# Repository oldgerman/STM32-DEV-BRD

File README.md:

# STM32-DEV-BRD

（白嫖失败血压升高后）整的几片考究的STM32最小系统板，~~清一色0603~~，确保食用舒适

PCB工程完全开源，提供测试程序，焊接后第一时间可刷入测试

## 型号

- 💚：完工并已验证
- :yellow_heart:：完工但未验证
- :x:：还没画板子

| 更新日期   | 状态           | 开发板型号                                                   | 支持芯片                                                 | PCB层数 |
| ---------- | -------------- | ------------------------------------------------------------ | -------------------------------------------------------- | ------- |
| 2022/04/29 | 💚              | [G031 DEV BRD](https://github.com/oldgerman/STM32-DEV-BRD/tree/master/G031_Dev) | STM32G031G8Ux                                            | 2       |
| 2022/04/29 | 💚              | [F4x1 DEV BRD](https://github.com/oldgerman/STM32-DEV-BRD/tree/master/F4x1_Dev) | STM32F401CxUx<br />STM32F411CxUx                         | 4       |
| 2022/07/31 | :yellow_heart: | [H7xxVxT6_LANG](https://github.com/oldgerman/STM32-DEV-BRD/tree/master/H7xxVxT6_LANG) | （LQFP100）<br />STM32H750<br />STM32H743<br />STM32H7B0 | 2       |
| ?          | :x:            | F07x DEV BRD                                                 | STM32F071CxUx<br />STM32F072CxUx                         | ?       |
| ?          | :x:            | F103 DEV BRD                                                 | STM32F103CxUx                                            | ?       |
| 2024/02/29 | 💚              | [G431 DEV BRD](https://github.com/oldgerman/STM32-DEV-BRD/tree/master/G431_Dev) | STM32G431GBUx                                            | 4       |
| ?          | ...            | （不定期更新）                                               |                                                          |         |

## PCB

| 开发板型号   | Top                                                          | Bottom                                                       |
| ------------ | ------------------------------------------------------------ | ------------------------------------------------------------ |
| G031 DEV BRD |  |  |
| F4x1 DEV BRD |  |  |
| G431 DEV BRD |  |  |

## 图片

.jpeg)

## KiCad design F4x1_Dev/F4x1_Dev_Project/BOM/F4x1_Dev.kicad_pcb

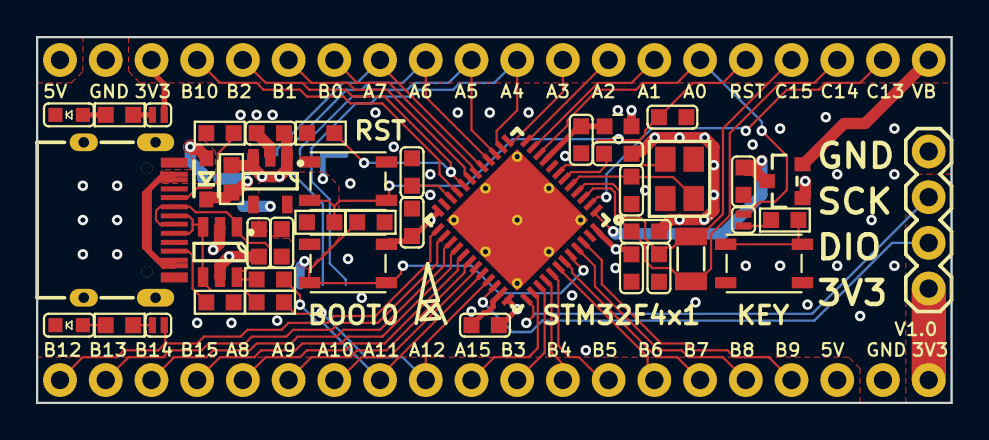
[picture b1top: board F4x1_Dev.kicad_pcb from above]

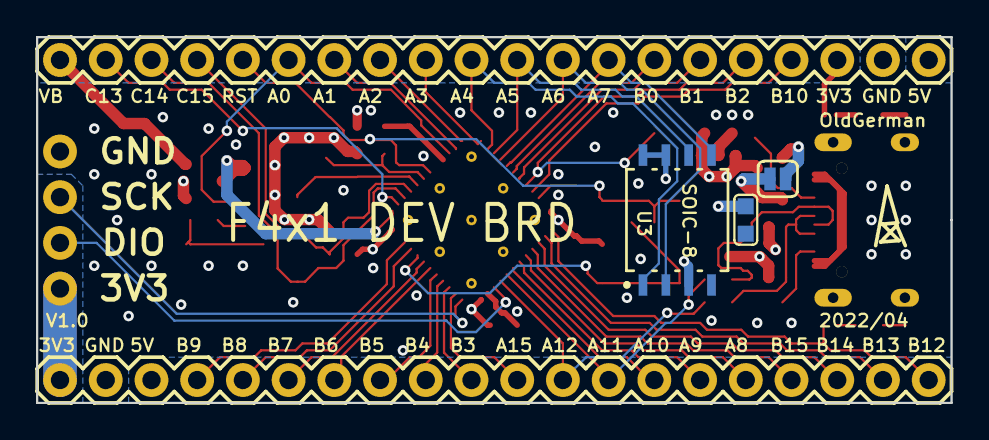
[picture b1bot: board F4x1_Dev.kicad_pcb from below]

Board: 4 copper layers, 50.8 x 20.3 mm, 50 parts (6 on the bottom side), 57 nets.

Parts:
*1, *2: ODG_LOGO; ODG_LOGO_1
C1, C4, C5, C6, C9, C14, C15: 100nF; C0603_1
C2, C3: 1uF/X7R; C0603_1
C7: 100nF; C0603_2
C8, C10: 6pF; C0603_1
C11, C13: 10pF; C0603_1
C12: 2.2uF; C0603_1
D1: B5819W; SOD-323_1
F1: 6V/0.5A; FUSE0603_0.5MM_1
L1: 10uH; FER0603_1
LED1: LED; LED0603_GREEN_1
LED2: LED; LED0603_YELLOW_1
P1, P2: CONN_X20; 2.54MM_MALE_X20_1
P3: CONN_X4; 2.54mm_Male_x4_1
R1, R2, R3, R4: 5.1K; R0603_1
R5, R6: 22R; R0603_1
R7: 330R; R0603_1
R8, R9, R10: 10K; R0603_1
SJ1: SJ_2P; SJ_2P_1
SJ2, SJ3, SJ4: SJ_2P; SJ_2P_MINI_1
SW1, SW2, SW3: Button-4P; SWITCH_3X4X2.5_4PIN_SMD_1
U1: STM32F4x1CxU6; UFQFPN-48_7X7X0P55MM_VIA_1
U2: ME6211C33M5G; ANALOG_TSOT-23-5_UJ-5_1
U3: W25Q32JVSSIQ; WIN_SS-8_WIN-L_1
USB1: Type-C; Type-C-TOP_1
VD1: BAT54C; ON_SEMI_SOT-23-3_1
VD2: USBLC6-2; MICROCHIP_SOT-23-6_M6_1
X1: 32.768KHz; XTAL_2P_3215_1
X2: 8MHz; EPSON_TSX-3225_1

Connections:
+3V3: C3.2, C4.2, C5.1, C6.1, C15.2, L1.1, P1.20, P2.3, P3.1, R9.1, SJ2.1, SW3.3, SW3.4, U1.24, U1.36, U1.48, U2.5, U3.3, U3.7, U3.8, VD1.1
+5: D1.1, SJ1.1, USB1.A4, USB1.A9, USB1.B4, USB1.B9
BOOT0: R10.1, SW3.1, SW3.2, U1.44
D+: R6.1, USB1.A6, USB1.B6, VD2.3, VD2.4
D-: R5.1, USB1.A7, USB1.B7, VD2.1, VD2.6
F_CS: P2.11, U1.14, U3.1
GND: C1.2, C2.1, C3.1, C4.1, C5.2, C6.2, C7.1, C8.2, C9.1, C10.2, C11.2, C12.1, C13.2, C14.1, C15.1, LED1.2, LED2.2, P1.19, P2.2, P3.4, R1.1, R3.2, R8.2, R10.2, SW1.3, SW1.4, SW2.1, SW2.2, U1.8, U1.23, U1.35, U1.47, U1.49, U1.49_1, U1.49_2, U1.49_3, U1.49_4, U1.49_5, U1.49_6, U1.49_7, U1.49_8, U1.49_9, U2.2, U3.4, USB1.1, USB1.2, USB1.3, USB1.4, USB1.A1, USB1.A12, USB1.B1, USB1.B12, VD2.2, X2.2, X2.4
MISO: P2.9, U1.16, U3.2
MOSI: P2.8, U1.17, U3.5
NRST: C14.2, P2.16, R9.2, SW2.3, SW2.4, U1.7
NetC12_2: C12.2, U1.22
NetD1_2: D1.2, F1.1, SJ1.2
NetLED1_1: LED1.1, R2.2
NetLED2_1: LED2.1, R4.2
NetR1_2: R1.2, USB1.A5
NetR2_1: R2.1, SJ2.2
NetR3_1: R3.1, USB1.B5
NetR4_1: R4.1, SJ3.2
NetR7_1: R7.1, SW1.1, SW1.2
NetR7_2: R7.2, SJ4.2
PA0: P2.15, SJ4.1, U1.10
PA1: P2.14, U1.11
PA2: P2.13, U1.12
PA3: P2.12, U1.13
PA5: P2.10, U1.15, U3.6
PA8: P1.5, U1.29
PA9: P1.6, U1.30
PA10: P1.7, U1.31
PA11: P1.8, R5.2, U1.32
PA12: P1.9, R6.2, U1.33
PA13: P3.2, U1.34
PA14: P3.3, U1.37
PA15: P1.10, U1.38
PB0: P2.7, U1.18
PB1: P2.6, U1.19
PB2: P2.5, R8.1, U1.20
PB3: P1.11, U1.39
PB4: P1.12, U1.40
PB5: P1.13, U1.41
PB6: P1.14, U1.42
PB7: P1.15, U1.43
PB8: P1.16, U1.45
PB9: P1.17, U1.46
PB10: P2.4, U1.21
PB12: P1.1, SJ3.1, U1.25
PB13: P1.2, U1.26
PB14: P1.3, U1.27
PB15: P1.4, U1.28
PC13: P2.19, U1.2
PC14: C8.1, P2.18, U1.3, X1.1
PC15: C10.1, P2.17, U1.4, X1.2
PH0: C11.1, U1.5, X2.1
PH1: C13.1, U1.6, X2.3
VB: P2.20, VD1.2
VBAT: C1.1, U1.1, VD1.3
VCC: C2.2, C9.2, F1.2, P1.18, P2.1, U2.1, U2.3, VD2.5
VREF+: C7.2, L1.2, U1.9

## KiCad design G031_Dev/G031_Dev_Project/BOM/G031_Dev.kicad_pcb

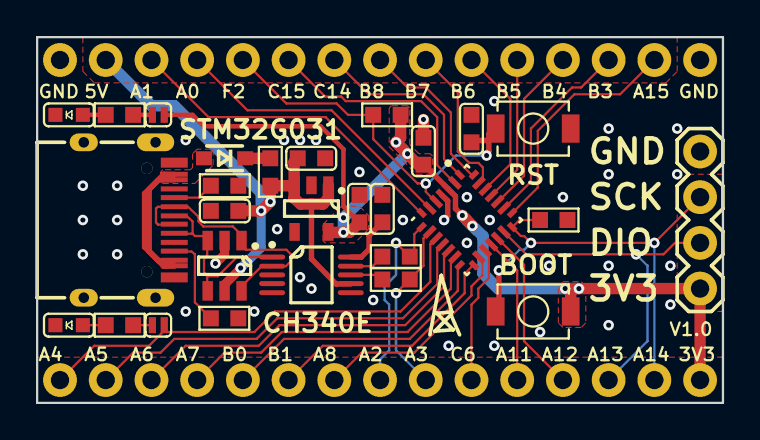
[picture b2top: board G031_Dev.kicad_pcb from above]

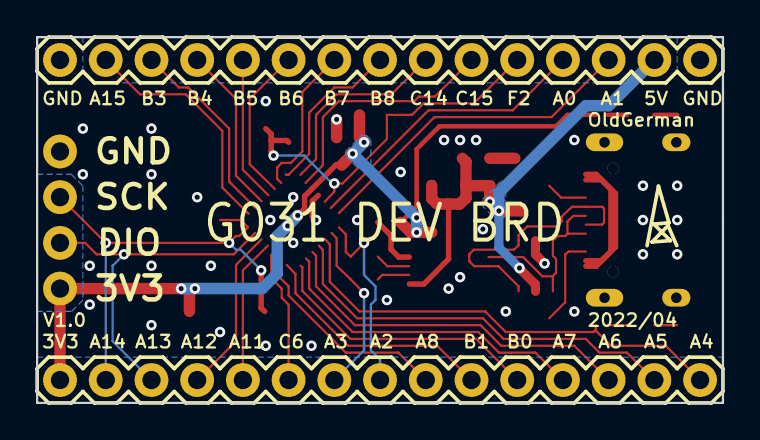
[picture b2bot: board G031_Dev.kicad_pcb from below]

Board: 2 copper layers, 38.1 x 20.3 mm, 32 parts (3 on the bottom side), 42 nets.

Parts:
*, *2: ODG_LOGO; ODG_LOGO_1
C1, C3, C4: 100nF; C0603_1
C2: 1uF/X7R; C0603_2
C5, C6: 1uF/X7R; C0603_1
D1: B5819W; SOD-323_1
F1: 6V/0.5A; FUSE0603_0.5MM_1
LED1: LED; LED0603_GREEN_1
LED2: LED; LED0603_YELLOW_1
P1: CONN_X4; 2.54mm_Male_x4_1
P2, P3: CONN_X15; 2.54MM_MALE_X15_1
R1, R2, R3, R8: 5.1K; R0603_1
R4, R5: 470R; R0603_1
R6, R7: 10K; R0603_1
SJ1, SJ2: SJ_2P; SJ_2P_MINI_1
SW1, SW2: Button-2P; SWITCH_3X4_SMD_1
U1: STM32G031G8U6; UFQFPN28-4x4mm_ODG_1
U2: CH340E; TI_MSOP-10_DGS_1
U3: ME6211C33M5G; ANALOG_TSOT-23-5_UJ-5_1
USB1: Type-C; Type-C-TOP_1
VD1: USBLC6-2; MICROCHIP_SOT-23-6_M6_1

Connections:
+3V3: C2.1, C6.2, P1.1, P2.15, R6.1, SJ1.1, SW1.2, U1.3, U3.5
+5: D1.1, USB1.A4, USB1.A9, USB1.B4, USB1.B9
CH340E_RX: R5.1, U2.9
CH340E_TX: R4.1, U2.8
D+: U2.1, USB1.A6, USB1.B6, VD1.3, VD1.4
D-: U2.2, USB1.A7, USB1.B7, VD1.1, VD1.6
GND: C1.1, C2.2, C3.1, C4.1, C5.1, C6.1, LED1.2, LED2.2, P1.4, P3.1, P3.15, R2.1, R3.2, R7.2, SW2.1, U1.4, U2.3, U3.2, USB1.1, USB1.2, USB1.3, USB1.4, USB1.A1, USB1.A12, USB1.B1, USB1.B12, VD1.2
NetC1_2: C1.2, U2.10
NetD1_2: D1.2, F1.1
NetLED1_1: LED1.1, R1.2
NetLED2_1: LED2.1, R8.2
NetR1_1: R1.1, SJ1.2
NetR2_2: R2.2, USB1.A5
NetR3_1: R3.1, USB1.B5
NetR8_1: R8.1, SJ2.2
PA0: P3.4, U1.6
PA1: P3.3, U1.7
PA2_TX: P2.8, R5.2, U1.8
PA3_RX: P2.9, R4.2, U1.9
PA4: P2.1, SJ2.1, U1.10
PA5: P2.2, U1.11
PA6: P2.3, U1.12
PA7: P2.4, U1.13
PA8: P2.7, U1.16
PA11: P2.11, U1.18
PA12: P2.12, U1.19
PA13_SWDIO: P1.2, P2.13, U1.20
PA14_SWCLK_B_O_O_T_0_: P1.3, P2.14, R7.1, SW1.1, U1.21
PA15: P3.14, U1.22
PB0: P2.5, U1.14
PB1: P2.6, U1.15
PB3: P3.13, U1.23
PB4: P3.12, U1.24
PB5: P3.11, U1.25
PB6: P3.10, U1.26
PB7: P3.9, U1.27
PB8: P3.8, U1.28
PC6: P2.10, U1.17
PC14: P3.7, U1.1
PC15: P3.6, U1.2
PF2_N_R_S_T_: C4.2, P3.5, R6.2, SW2.2, U1.5
VCC: C3.2, C5.2, F1.2, P3.2, U2.7, U3.1, U3.3, VD1.5

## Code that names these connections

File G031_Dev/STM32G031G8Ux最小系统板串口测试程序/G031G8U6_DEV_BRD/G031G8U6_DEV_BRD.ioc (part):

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Mcu.Name=STM32G031G(4-6-8)Ux
Mcu.Package=UFQFPN28
Mcu.UserName=STM32G031G8Ux
PA1.Mode=Full_Duplex_Master
PA1.Signal=SPI1_SCK
PA11\ [PA9].Mode=I2C
PA11\ [PA9].Signal=I2C2_SCL
PA12\ [PA10].Mode=I2C
PA12\ [PA10].Signal=I2C2_SDA
PA2.GPIOParameters=GPIO_Speed,GPIO_PuPd
PA2.GPIO_PuPd=GPIO_NOPULL
PA2.GPIO_Speed=GPIO_SPEED_FREQ_HIGH
PA2.Mode=Asynchronous
PA2.Signal=USART2_TX
PA3.GPIOParameters=GPIO_Speed
PA3.GPIO_Speed=GPIO_SPEED_FREQ_HIGH
PA3.Mode=Asynchronous
PA3.Signal=USART2_RX
PA4.GPIOParameters=GPIO_Label
PA4.GPIO_Label=LED
PA4.Signal=GPIO_Output
PA6.Mode=Full_Duplex_Master
PA6.Signal=SPI1_MISO
PA7.Mode=Full_Duplex_Master
PA7.Signal=SPI1_MOSI
PB3.Signal=S_TIM2_CH2
PB6.Mode=I2C
PB6.Signal=I2C1_SCL
PB7.Mode=I2C
PB7.Signal=I2C1_SDA
RCC.HSE_VALUE=8000000
RCC.SYSCLKFreq_VALUE=64000000
RCC.SYSCLKSource=RCC_SYSCLKSOURCE_PLLCLK
board=custom

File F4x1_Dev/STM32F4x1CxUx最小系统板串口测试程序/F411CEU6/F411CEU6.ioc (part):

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Mcu.Name=STM32F411C(C-E)Ux
Mcu.Package=UFQFPN48
Mcu.UserName=STM32F411CEUx
PA0-WKUP.GPIOParameters=GPIO_PuPd,GPIO_Label
PA0-WKUP.GPIO_Label=KEY
PA0-WKUP.GPIO_PuPd=GPIO_PULLUP
PA0-WKUP.Signal=GPIO_Input
PA11.Mode=Device_Only
PA11.Signal=USB_OTG_FS_DM
PA12.Mode=Device_Only
PA12.Signal=USB_OTG_FS_DP
PA13.Mode=Trace_Asynchronous_SW
PA13.Signal=SYS_JTMS-SWDIO
PA14.Mode=Trace_Asynchronous_SW
PA14.Signal=SYS_JTCK-SWCLK
PB12.GPIOParameters=GPIO_Label
PB12.GPIO_Label=LED
PB12.Signal=GPIO_Output
PB3.Mode=Trace_Asynchronous_SW
PB3.Signal=SYS_JTDO-SWO
PH0\ -\ OSC_IN.Mode=HSE-External-Oscillator
PH0\ -\ OSC_IN.Signal=RCC_OSC_IN
PH1\ -\ OSC_OUT.Mode=HSE-External-Oscillator
PH1\ -\ OSC_OUT.Signal=RCC_OSC_OUT
RCC.HSE_VALUE=8000000
RCC.SYSCLKFreq_VALUE=96000000
RCC.SYSCLKSource=RCC_SYSCLKSOURCE_PLLCLK
board=custom

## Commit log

2022-04-27 删除多余的history文件
2022-07-31 添加 H7xxVxT6_LANG 开发板
2022-07-31 修改README
2022-07-31 添加H750VBTx_LANG_BTB_IO.ioc，标记双排母引出的io
2022-07-31 添加H750VBTx_LANG双排母引出的io图片
2022-07-31 添加H750VBTx_LANG双排母引出的io图片x2
2022-08-04 H7xxVxT6_LANG添加BOM
2024-02-29 2024-02-29_18:56
2024-04-22 2024-0422_18:15
